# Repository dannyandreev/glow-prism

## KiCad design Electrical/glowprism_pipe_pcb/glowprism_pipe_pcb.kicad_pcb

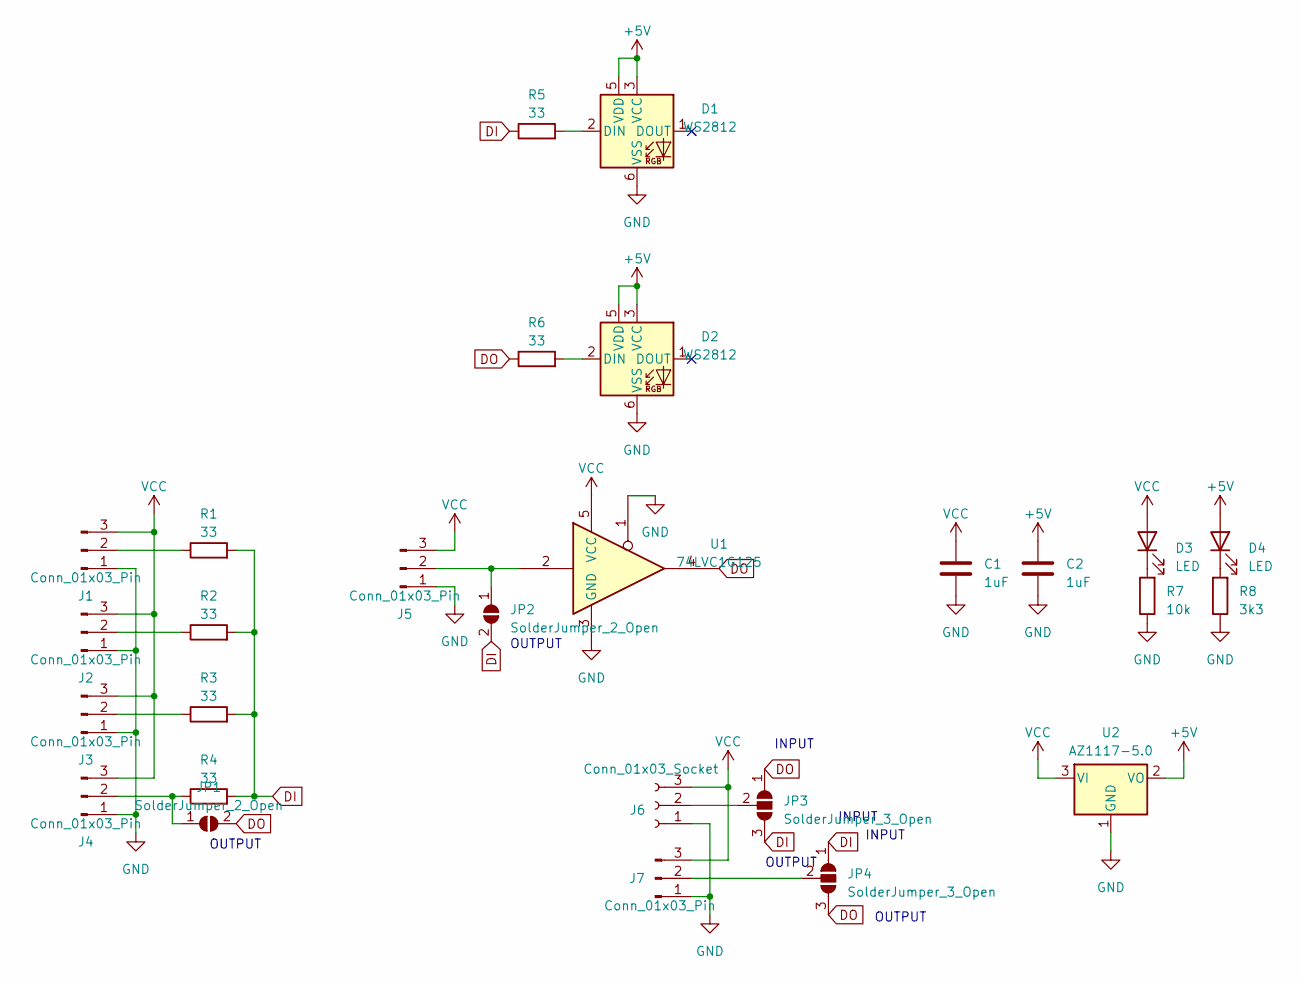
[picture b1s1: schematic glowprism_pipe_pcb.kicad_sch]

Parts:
C1, C2: 1uF; C_0805_2012Metric
D1, D2: WS2812; LED_WS2812_PLCC6_5.0x5.0mm_P1.6mm
D3, D4: LED; D_0805_2012Metric
J1, J2, J3, J4, J5: Conn_01x03_Pin; JST_XH_B3B-XH-A_1x03_P2.50mm_Vertical
J6: Conn_01x03_Socket; amass mr30
J7: Conn_01x03_Pin; amass mr30
JP1, JP2: SolderJumper_2_Open; SolderJumper-2_P1.3mm_Open_RoundedPad1.0x1.5mm
JP3, JP4: SolderJumper_3_Open; SolderJumper-3_P1.3mm_Open_RoundedPad1.0x1.5mm
R1, R2, R3, R4, R5, R6: 33; R_0805_2012Metric
R7: 10k; R_0805_2012Metric
R8: 3k3; R_0805_2012Metric
U1: 74LVC1G125; SOT-353_SC-70-5
U2: AZ1117-5.0; SOT-223-3_TabPin2

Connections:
+5V: C2.1, D1.3 (VCC), D1.5 (VDD), D2.3 (VCC), D2.5 (VDD), D4.2 (A), U2.2 (VO)
DI: JP2.2 (B), JP3.3 (B), JP4.1 (A), R1.2, R2.2, R3.2, R4.2, R5.1
DO: JP1.2 (B), JP3.1 (A), JP4.3 (B), R6.1, U1.4
GND: C1.2, C2.2, D1.6 (VSS), D2.6 (VSS), J1.1, J2.1, J3.1, J4.1, J5.1, J6.1, J7.1, R7.1, R8.1, U1.1, U1.3 (GND), U2.1 (GND)
unnamed: D1.2 (DIN), R5.2
unnamed: D2.2 (DIN), R6.2
unnamed: D3.1 (K), R7.2
unnamed: D4.1 (K), R8.2
unnamed: J1.2, R1.1
unnamed: J2.2, R2.1
unnamed: J3.2, R3.1
unnamed: J4.2, JP1.1 (A), R4.1
unnamed: J5.2, JP2.1 (A), U1.2
unnamed: J6.2, JP3.2 (C)
unnamed: J7.2, JP4.2 (C)
VCC: C1.1, D3.2 (A), J1.3, J2.3, J3.3, J4.3, J5.3, J6.3, J7.3, U1.5 (VCC), U2.3 (VI)

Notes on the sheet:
OUTPUT
INPUT

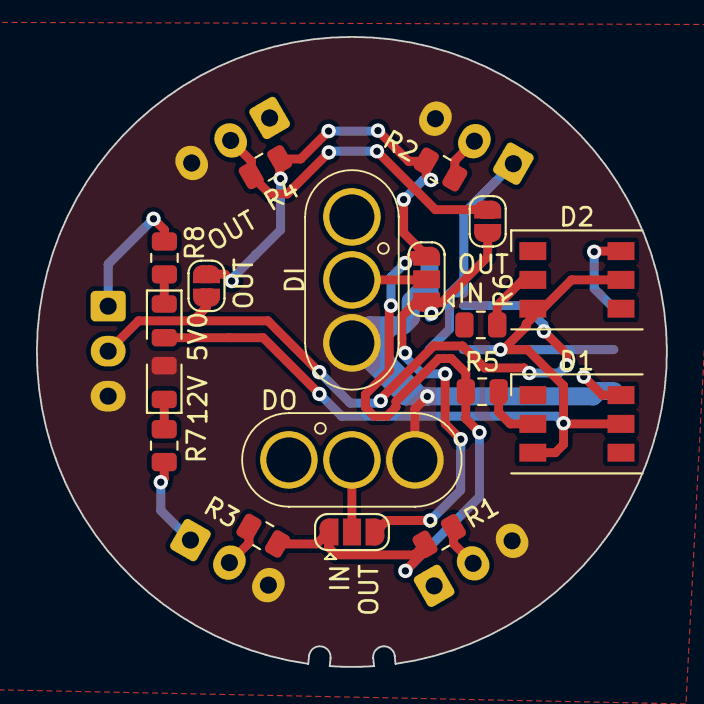
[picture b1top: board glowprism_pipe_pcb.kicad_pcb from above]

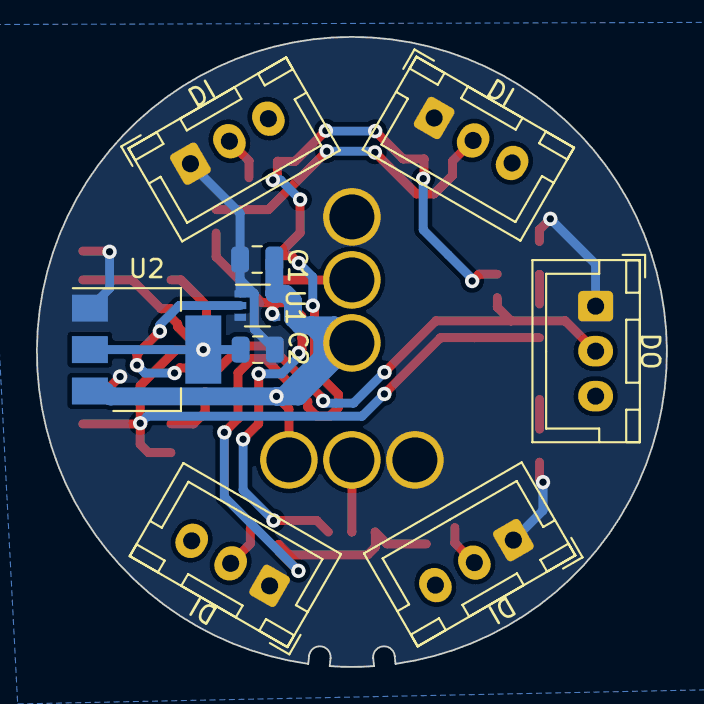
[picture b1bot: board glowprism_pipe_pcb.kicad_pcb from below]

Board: 2 copper layers, 35.0 x 35.0 mm, 27 parts (9 on the bottom side), 16 nets.

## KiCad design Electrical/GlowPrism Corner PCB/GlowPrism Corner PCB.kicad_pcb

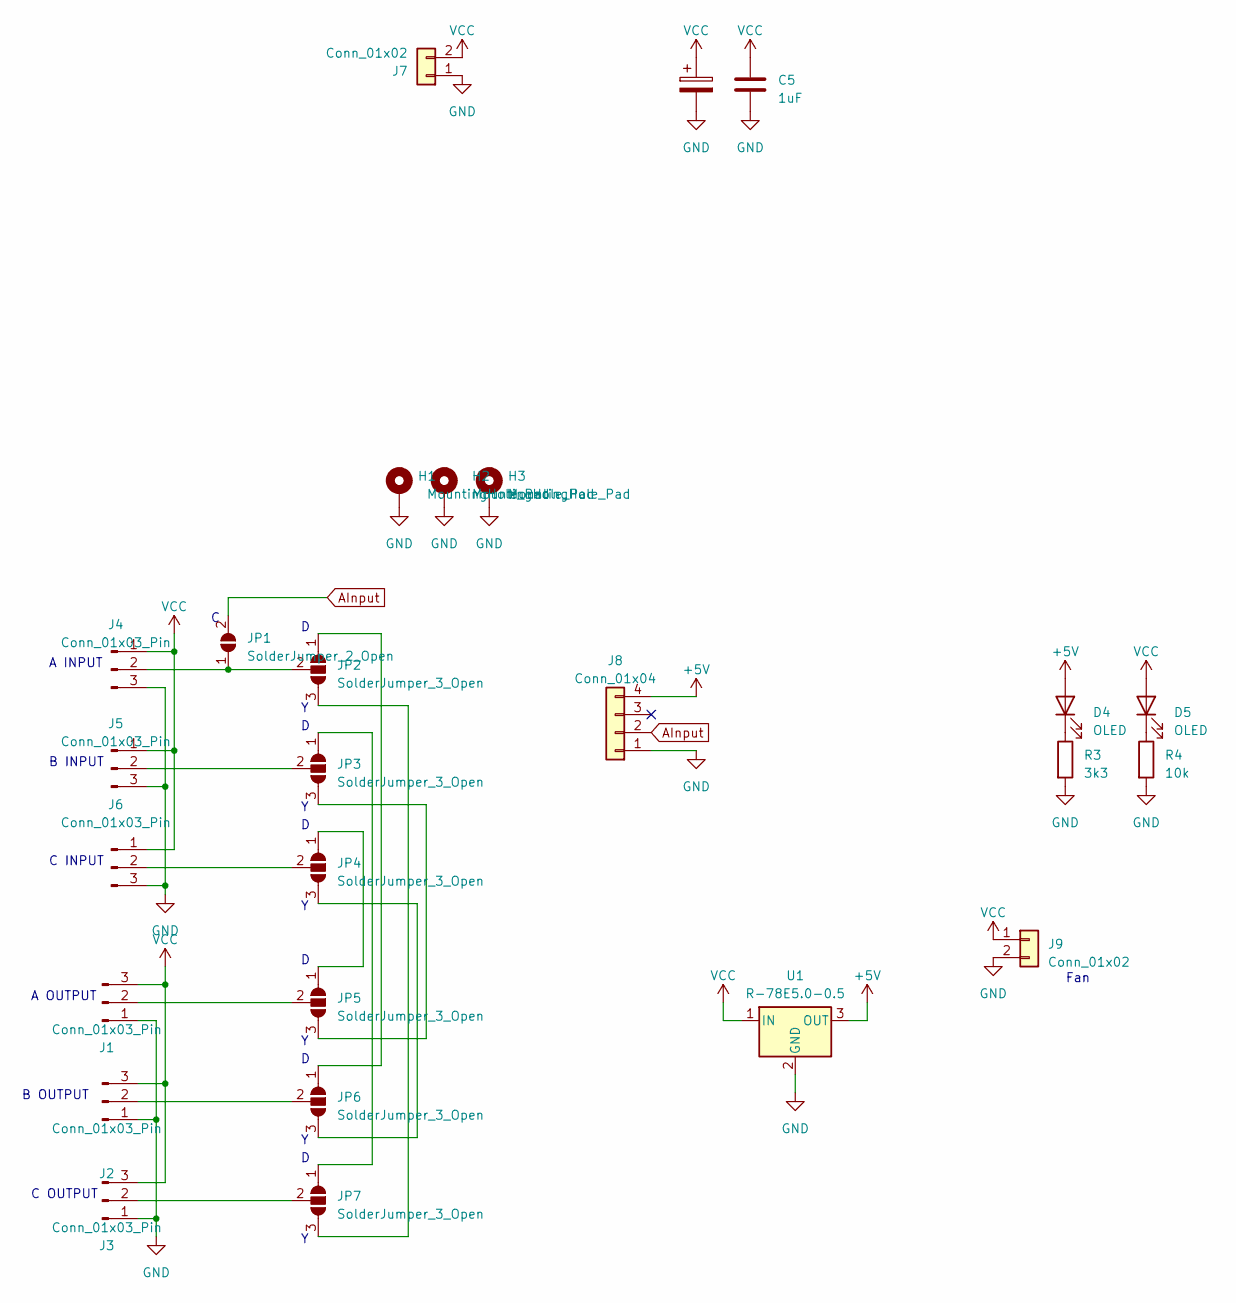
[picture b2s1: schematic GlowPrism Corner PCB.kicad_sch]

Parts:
C3: 47uF; CP_Elec_6.3x5.9
C5: 1uF; C_0805_2012Metric
D4, D5: OLED; LED_0805_2012Metric
H1, H2, H3: MountingHole_Pad; MountingHole_3.2mm_M3_DIN965_Pad
J1, J2, J3, J4, J5, J6: Conn_01x03_Pin; 3 Pad Input
J7: Conn_01x02; AMASS_XT60-M_1x02_P7.20mm_Vertical
J8: Conn_01x04; PinSocket_1x04_P2.54mm_Vertical
J9: Conn_01x02; JST_XH_B2B-XH-A_1x02_P2.50mm_Vertical
JP1: SolderJumper_2_Open; SolderJumper-2_P1.3mm_Open_RoundedPad1.0x1.5mm
JP2, JP3, JP4, JP5, JP6, JP7: SolderJumper_3_Open; SolderJumper-3_P1.3mm_Open_RoundedPad1.0x1.5mm
R3: 3k3; C_0805_2012Metric
R4: 10k; C_0805_2012Metric
U1: R-78E5.0-0.5; Converter_DCDC_RECOM_R-78E-0.5_THT

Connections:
+5V: D4.2 (A), J8.4, U1.3 (OUT)
AInput: J8.2, JP1.2 (B)
GND: C3.2, C5.2, H1.1, H2.1, H3.1, J1.1, J2.1, J3.1, J4.3, J5.3, J6.3, J7.1, J8.1, J9.2, R3.2, R4.2, U1.2 (GND)
unnamed: D4.1 (K), R3.1
unnamed: D5.1 (K), R4.1
unnamed: J1.2, JP5.2 (C)
unnamed: J2.2, JP6.2 (C)
unnamed: J3.2, JP7.2 (C)
unnamed: J4.2, JP1.1 (A), JP2.2 (C)
unnamed: J5.2, JP3.2 (C)
unnamed: J6.2, JP4.2 (C)
unnamed: JP2.1 (A), JP6.1 (A)
unnamed: JP2.3 (B), JP7.3 (B)
unnamed: JP3.1 (A), JP7.1 (A)
unnamed: JP3.3 (B), JP5.3 (B)
unnamed: JP4.1 (A), JP5.1 (A)
unnamed: JP4.3 (B), JP6.3 (B)
VCC: C3.1, C5.1, D5.2 (A), J1.3, J2.3, J3.3, J4.1, J5.1, J6.1, J7.2, J9.1, U1.1 (IN)

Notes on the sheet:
A INPUT
A OUTPUT
Fan
B OUTPUT
C INPUT
B INPUT
C OUTPUT

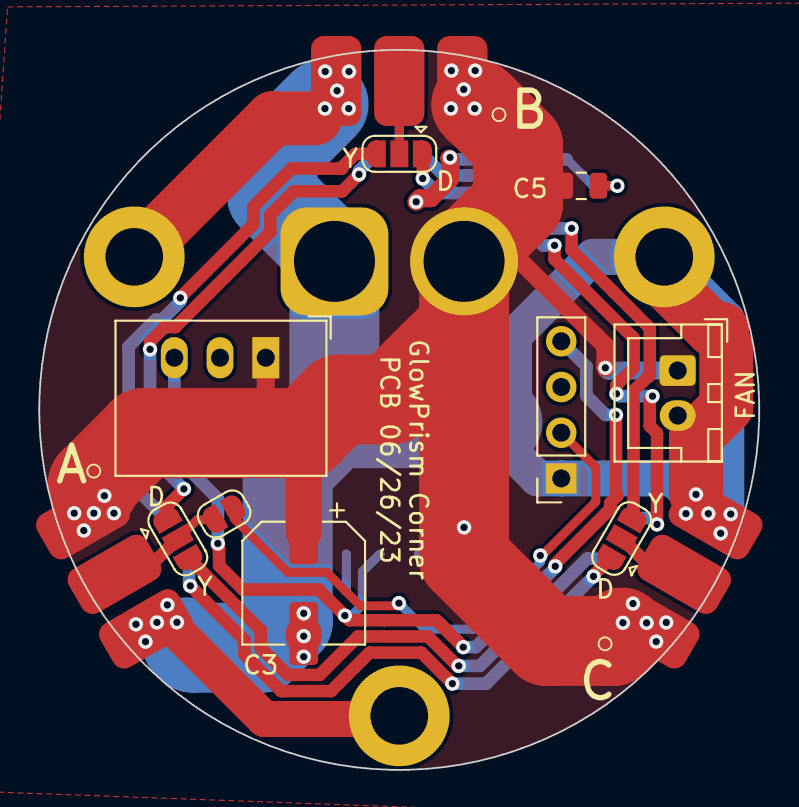
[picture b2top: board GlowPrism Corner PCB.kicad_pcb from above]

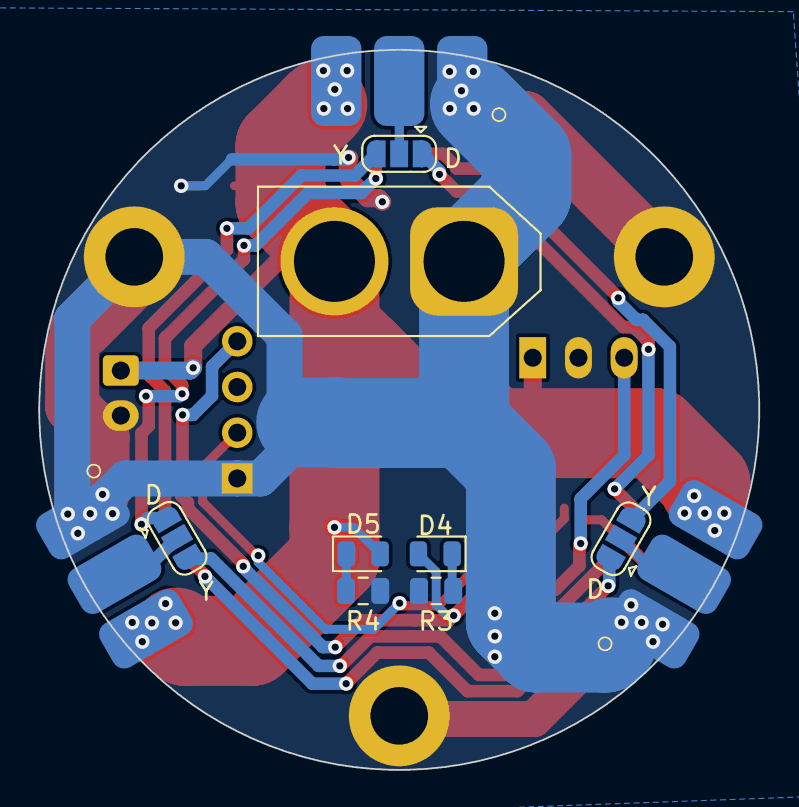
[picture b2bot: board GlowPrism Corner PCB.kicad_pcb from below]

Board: 2 copper layers, 40.0 x 40.0 mm, 26 parts (11 on the bottom side), 18 nets.

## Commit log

2023-06-30 prism PCBs done and endcap
2023-07-08 pyramid v1 done
